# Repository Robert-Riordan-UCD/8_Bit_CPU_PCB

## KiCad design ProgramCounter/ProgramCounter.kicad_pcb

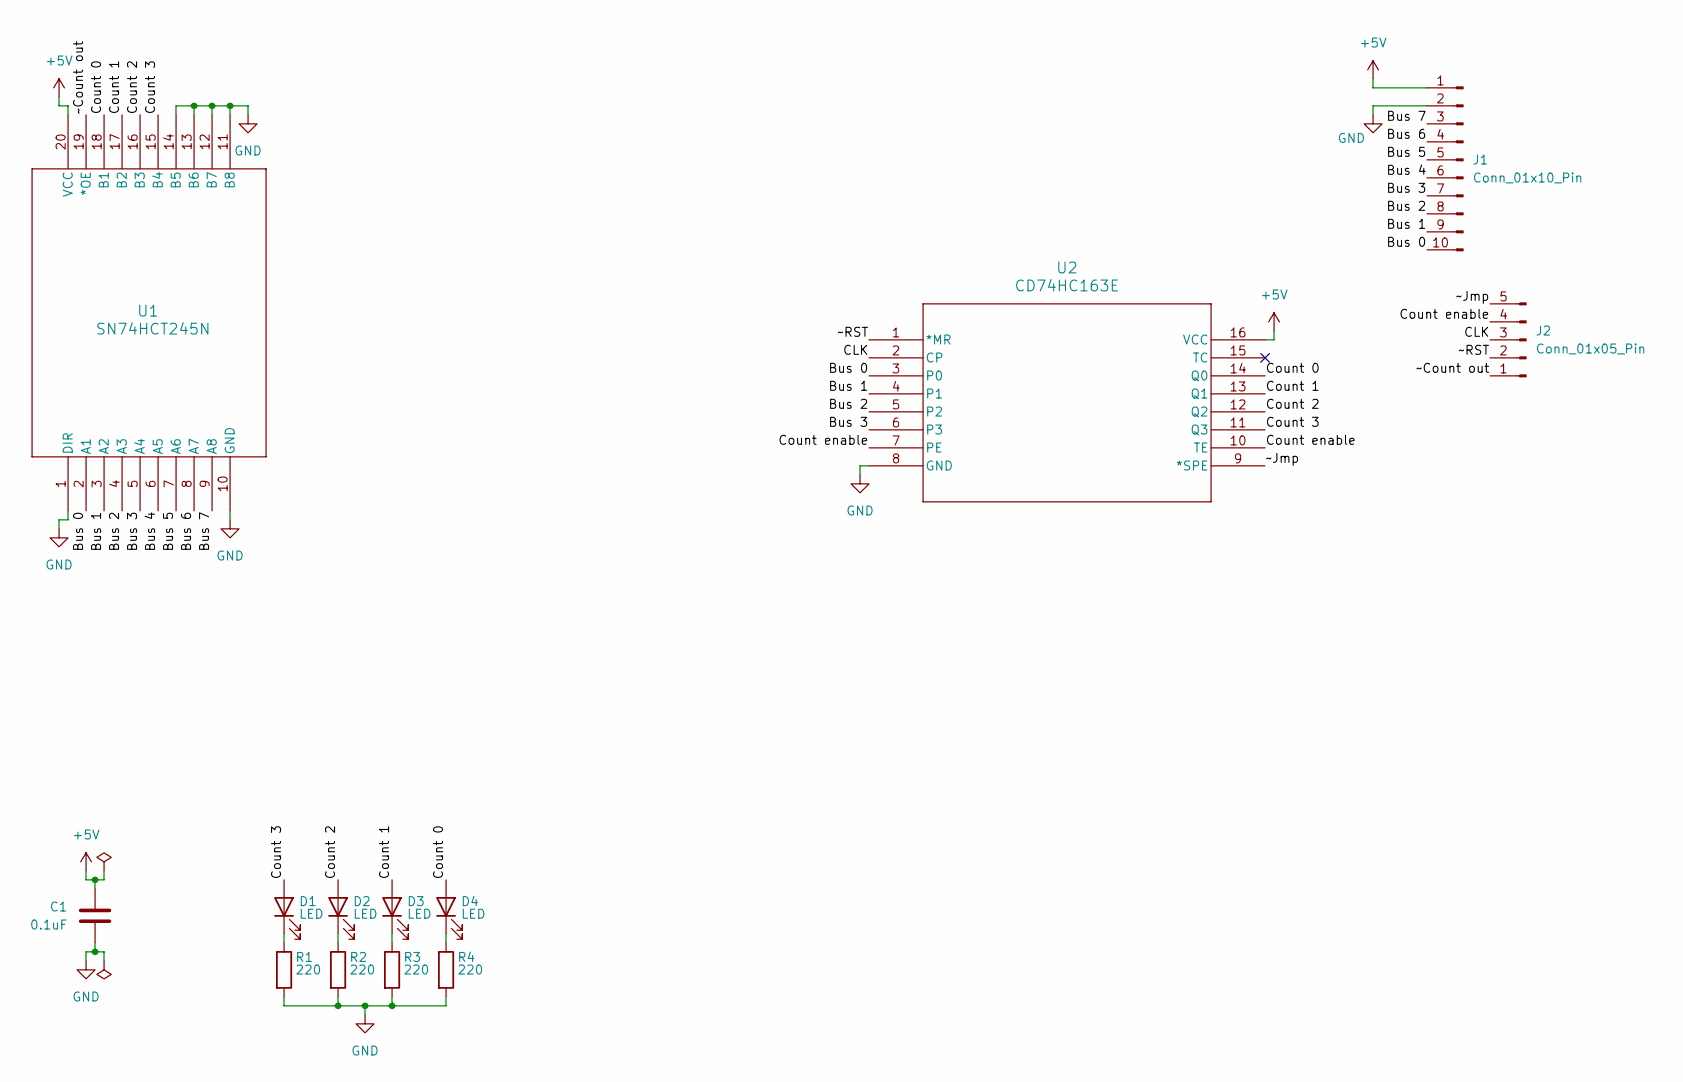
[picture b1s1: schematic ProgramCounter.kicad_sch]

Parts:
C1: 0.1uF; C_Disc_D5.0mm_W2.5mm_P2.50mm
D1, D2, D3, D4: LED; LED_D5.0mm
J1: Conn_01x10_Pin; PinHeader_1x10_P2.54mm_Vertical
J2: Conn_01x05_Pin; PinHeader_1x05_P2.54mm_Vertical
R1, R2, R3, R4: 220; CF_series_Resistors_THT
U1: SN74HCT245N; 8x_tristate_transceiver
U2: CD74HC163E; binary_counter

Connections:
+5V: C1.1, J1.1, U1.20 (VCC), U2.16 (VCC)
/Bus 0: J1.10, U1.2 (A1), U2.3 (P0)
/Bus 1: J1.9, U1.3 (A2), U2.4 (P1)
/Bus 2: J1.8, U1.4 (A3), U2.5 (P2)
/Bus 3: J1.7, U1.5 (A4), U2.6 (P3)
/Bus 4: J1.6, U1.6 (A5)
/Bus 5: J1.5, U1.7 (A6)
/Bus 6: J1.4, U1.8 (A7)
/Bus 7: J1.3, U1.9 (A8)
/CLK: J2.3, U2.2 (CP)
/Count 0: D4.2 (A), U1.18 (B1), U2.14 (Q0)
/Count 1: D3.2 (A), U1.17 (B2), U2.13 (Q1)
/Count 2: D2.2 (A), U1.16 (B3), U2.12 (Q2)
/Count 3: D1.2 (A), U1.15 (B4), U2.11 (Q3)
/Count enable: J2.4, U2.7 (PE), U2.10 (TE)
/~Count out: J2.1, U1.19 (*OE)
/~Jmp: J2.5, U2.9 (*SPE)
/~RST: J2.2, U2.1 (*MR)
GND: C1.2, J1.2, R1.2, R2.2, R3.2, R4.2, U1.1 (DIR), U1.10 (GND), U1.11 (B8), U1.12 (B7), U1.13 (B6), U1.14 (B5), U2.8 (GND)
unnamed: D1.1 (K), R1.1
unnamed: D2.1 (K), R2.1
unnamed: D3.1 (K), R3.1
unnamed: D4.1 (K), R4.1

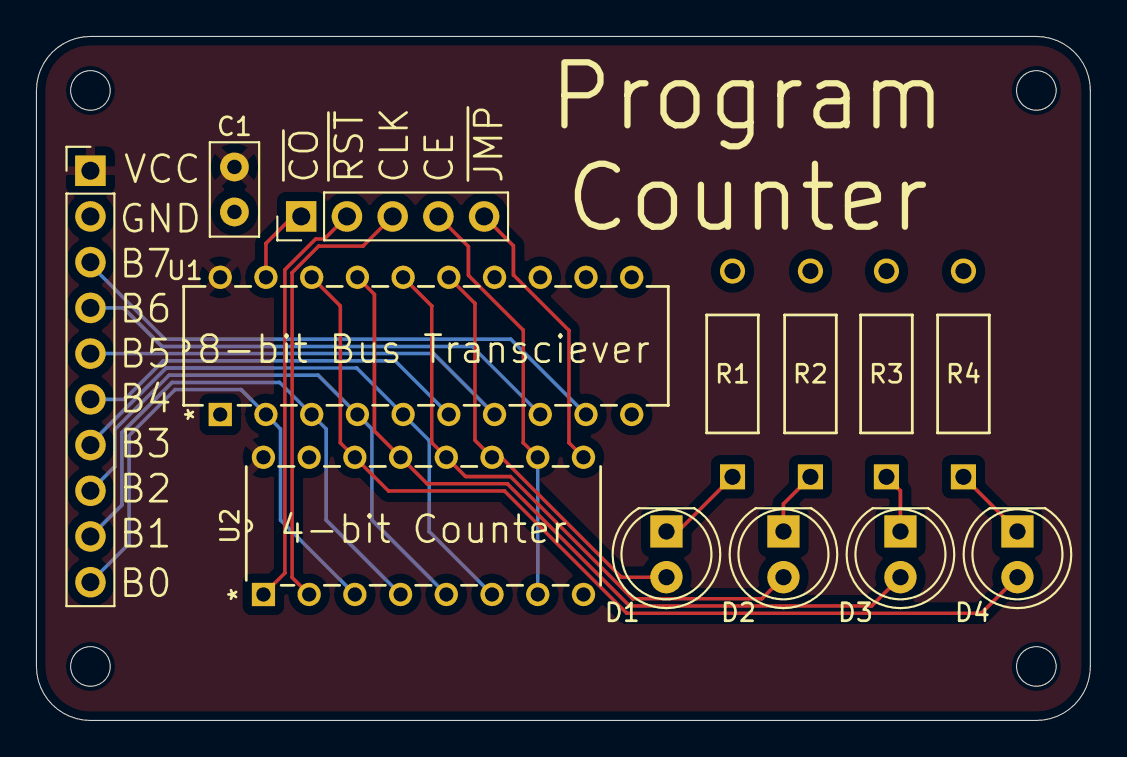
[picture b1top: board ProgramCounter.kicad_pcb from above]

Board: 2 copper layers, 58.6 x 38.0 mm, 13 parts (0 on the bottom side), 23 nets.
